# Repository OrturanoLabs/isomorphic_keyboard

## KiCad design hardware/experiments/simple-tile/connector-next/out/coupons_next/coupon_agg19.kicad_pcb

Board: 2 copper layers, 46 parts (0 on the bottom side), 19 nets.

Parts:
PB_W: PB_W
PB_clk: PB_clk
PB_data: PB_data
PB_first: PB_first
PB_latch: PB_latch
PGND: PGND
PGND_DET_B: PGND_DET_B
PGND_DET_R: PGND_DET_R
PGND_DET_T: PGND_DET_T
PL_clk: PL_clk
PL_data: PL_data
PL_endrow: PL_endrow
PL_latch: PL_latch
PR_latch: PR_latch
PT_W: PT_W
PT_clk: PT_clk
PT_data: PT_data
PT_endcol: PT_endcol
PVCC: PVCC
SW00, SW10, SW11, SW20, SW21, SW30, SW31: SW_Hotswap_Kailh_MX_1.00u
SW01: SW_Hotswap_Kailh_MX_1.00u_EdgeTrim
TPB_W: TPB_W
TPB_clk: TPB_clk
TPB_data: TPB_data
TPB_first: TPB_first
TPB_latch: TPB_latch
TPGND: TPGND
TPGND_DET_B: TPGND_DET_B
TPGND_DET_R: TPGND_DET_R
TPGND_DET_T: TPGND_DET_T
TPL_clk: TPL_clk
TPL_data: TPL_data
TPL_endrow: TPL_endrow
TPL_latch: TPL_latch
TPR_latch: TPR_latch
TPT_W: TPT_W
TPT_clk: TPT_clk
TPT_data: TPT_data
TPT_endcol: TPT_endcol
TPVCC: TPVCC

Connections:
B_W: PB_W.1, TPB_W.1
B_clk: PB_clk.1, TPB_clk.1
B_data: PB_data.1, TPB_data.1
B_first: PB_first.1, TPB_first.1
B_latch: PB_latch.1, TPB_latch.1
GND: PGND.1, TPGND.1
GND_DET_B: PGND_DET_B.1, TPGND_DET_B.1
GND_DET_R: PGND_DET_R.1, TPGND_DET_R.1
GND_DET_T: PGND_DET_T.1, TPGND_DET_T.1
L_clk: PL_clk.1, TPL_clk.1
L_data: PL_data.1, TPL_data.1
L_endrow: PL_endrow.1, TPL_endrow.1
L_latch: PL_latch.1, TPL_latch.1
R_latch: PR_latch.1, TPR_latch.1
T_W: PT_W.1, TPT_W.1
T_clk: PT_clk.1, TPT_clk.1
T_data: PT_data.1, TPT_data.1
T_endcol: PT_endcol.1, TPT_endcol.1
VCC: PVCC.1, TPVCC.1

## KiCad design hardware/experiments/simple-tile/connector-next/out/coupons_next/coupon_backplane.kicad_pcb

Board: 2 copper layers, 111 parts (0 on the bottom side), 54 nets.

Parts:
PA0: PA0
PA1: PA1
PA2: PA2
PA3: PA3
PA4: PA4
PA5: PA5
PA6: PA6
PA7: PA7
PA8: PA8
PA9: PA9
PA10: PA10
PA11: PA11
PA12: PA12
PA13: PA13
PA14: PA14
PA15: PA15
PA16: PA16
PA17: PA17
PA18: PA18
PR0: PR0
PR1: PR1
PR2: PR2
PR3: PR3
PR4: PR4
PR5: PR5
PR6: PR6
PR7: PR7
PR8: PR8
PR9: PR9
PR10: PR10
PR11: PR11
PR12: PR12
PR13: PR13
PR14: PR14
PR15: PR15
PR16: PR16
PR17: PR17
PR18: PR18
PS0: PS0
PS1: PS1
PS2: PS2
PS3: PS3
PS4: PS4
PS5: PS5
PS6: PS6
PS7: PS7
PS8: PS8
PS9: PS9
PS10: PS10
PS11: PS11
PS12: PS12
PS13: PS13
PS14: PS14
PS15: PS15
PS16: PS16
PS17: PS17
PS18: PS18
TPAB_W: TPAB_W
TPAB_clk: TPAB_clk
TPAB_data: TPAB_data
TPAB_latch: TPAB_latch
TPAGND: TPAGND
TPAGND_DET_R: TPAGND_DET_R
TPAGND_DET_T: TPAGND_DET_T
TPAL_clk: TPAL_clk
TPAL_data: TPAL_data
TPAL_endrow: TPAL_endrow
TPAL_latch: TPAL_latch
TPAR_latch: TPAR_latch
TPAT_W: TPAT_W
TPAT_clk: TPAT_clk
TPAT_data: TPAT_data
TPAT_endcol: TPAT_endcol
TPAVCC: TPAVCC
TPDA.GND_DET_B: TPDA.GND_DET_B
TPDS.GND_DET_R: TPDS.GND_DET_R
TPDS.GND_DET_T: TPDS.GND_DET_T
TPRB_W: TPRB_W
TPRB_clk: TPRB_clk
TPRB_data: TPRB_data
TPRB_first: TPRB_first
TPRB_latch: TPRB_latch
TPRGND: TPRGND
TPRGND_DET_B: TPRGND_DET_B
TPRGND_DET_R: TPRGND_DET_R
TPRGND_DET_T: TPRGND_DET_T
TPRL_clk: TPRL_clk
TPRL_data: TPRL_data
TPRL_latch: TPRL_latch
TPRR_latch: TPRR_latch
TPRT_W: TPRT_W
TPRT_clk: TPRT_clk
TPRT_data: TPRT_data
TPRT_endcol: TPRT_endcol
TPRVCC: TPRVCC
TPSB_W: TPSB_W
TPSB_clk: TPSB_clk
TPSB_data: TPSB_data
TPSB_first: TPSB_first
TPSB_latch: TPSB_latch
TPSGND: TPSGND
TPSGND_DET_B: TPSGND_DET_B
TPSL_clk: TPSL_clk
TPSL_data: TPSL_data
TPSL_endrow: TPSL_endrow
TPSL_latch: TPSL_latch
TPSR_latch: TPSR_latch
TPST_W: TPST_W
TPST_clk: TPST_clk
TPST_data: TPST_data
TPSVCC: TPSVCC

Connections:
SA.B_W: PA13.1, TPAB_W.1
SA.B_clk: PA9.1, TPAB_clk.1
SA.B_data: PA10.1, TPAB_data.1
SA.B_latch: PA12.1, TPAB_latch.1
SA.GND: PA0.1, TPAGND.1
SA.GND_DET_R: PA3.1, TPAGND_DET_R.1
SA.GND_DET_T: PA1.1, TPAGND_DET_T.1
SA.L_clk: PA14.1, TPAL_clk.1
SA.L_data: PA15.1, TPAL_data.1
SA.L_endrow: PA16.1, TPAL_endrow.1
SA.L_latch: PA17.1, TPAL_latch.1
SA.R_latch: PA18.1, TPAR_latch.1
SA.T_W: PA8.1, TPAT_W.1
SA.T_clk: PA5.1, TPAT_clk.1
SA.T_data: PA6.1, TPAT_data.1
SA.T_endcol: PA7.1, TPAT_endcol.1
SA.VCC: PA4.1, TPAVCC.1
SR.B_W: PR13.1, TPRB_W.1
SR.B_clk: PR9.1, TPRB_clk.1
SR.B_data: PR10.1, TPRB_data.1
SR.B_first: PR11.1, TPRB_first.1
SR.B_latch: PR12.1, TPRB_latch.1
SR.GND: PR0.1, TPRGND.1
SR.GND_DET_B: PR2.1, TPRGND_DET_B.1
SR.GND_DET_R: PR3.1, TPRGND_DET_R.1
SR.GND_DET_T: PR1.1, TPRGND_DET_T.1
SR.L_clk: PR14.1, TPRL_clk.1
SR.L_data: PR15.1, TPRL_data.1
SR.L_latch: PR17.1, TPRL_latch.1
SR.R_latch: PR18.1, TPRR_latch.1
SR.T_W: PR8.1, TPRT_W.1
SR.T_clk: PR5.1, TPRT_clk.1
SR.T_data: PR6.1, TPRT_data.1
SR.T_endcol: PR7.1, TPRT_endcol.1
SR.VCC: PR4.1, TPRVCC.1
SS.B_W: PS13.1, TPSB_W.1
SS.B_clk: PS9.1, TPSB_clk.1
SS.B_data: PS10.1, TPSB_data.1
SS.B_first: PS11.1, TPSB_first.1
SS.B_latch: PS12.1, TPSB_latch.1
SS.GND: PS0.1, TPSGND.1
SS.GND_DET_B: PS2.1, TPSGND_DET_B.1
SS.L_clk: PS14.1, TPSL_clk.1
SS.L_data: PS15.1, TPSL_data.1
SS.L_endrow: PS16.1, TPSL_endrow.1
SS.L_latch: PS17.1, TPSL_latch.1
SS.R_latch: PS18.1, TPSR_latch.1
SS.T_W: PS8.1, TPST_W.1
SS.T_clk: PS5.1, TPST_clk.1
SS.T_data: PS6.1, TPST_data.1
SS.VCC: PS4.1, TPSVCC.1
STUBDET.A.GND_DET_B>S.T_endcol: PA2.1, PS7.1, TPDA.GND_DET_B.1
STUBDET.S.GND_DET_R>R.L_endrow: PR16.1, PS3.1, TPDS.GND_DET_R.1
STUBDET.S.GND_DET_T>A.B_first: PA11.1, PS1.1, TPDS.GND_DET_T.1

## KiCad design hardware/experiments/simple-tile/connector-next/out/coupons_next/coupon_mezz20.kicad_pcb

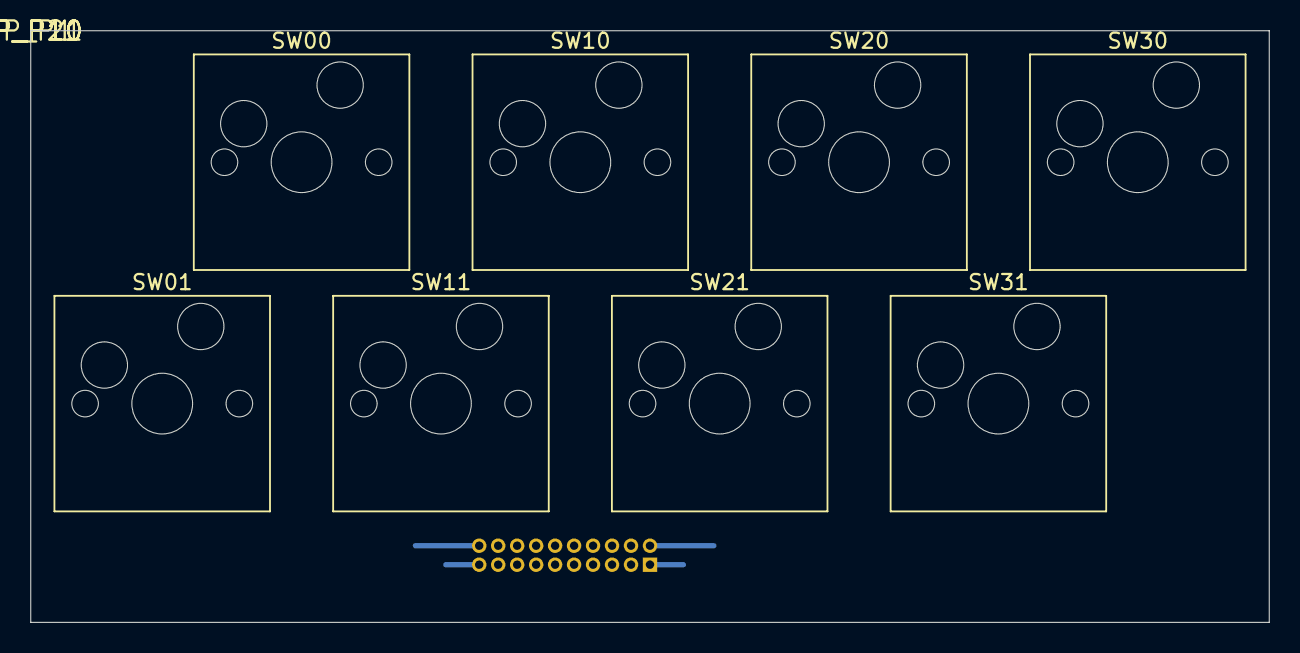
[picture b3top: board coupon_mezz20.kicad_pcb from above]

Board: 2 copper layers, 81.6 x 39.0 mm, 13 parts (1 on the bottom side), 4 nets.

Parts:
J1: G125-MVX2005L0X (tile plug, THT tails); Harwin_Gecko-G125-MVX2005L0X_2x10_P1.25mm_Vertical
SW00, SW10, SW11, SW20, SW21, SW30, SW31: SW_Hotswap_Kailh_MX_1.00u
SW01: SW_Hotswap_Kailh_MX_1.00u_EdgeTrim
TP_P1: TP_P1
TP_P10: TP_P10
TP_P11: TP_P11
TP_P20: TP_P20

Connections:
J1.B_W:10: J1.10, TP_P10.1
J1.GND:20: J1.20, TP_P20.1
J1.L_clk:11: J1.11, TP_P11.1
J1.VCC:1: J1.1, TP_P1.1

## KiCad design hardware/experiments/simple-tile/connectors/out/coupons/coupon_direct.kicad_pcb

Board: 2 copper layers, 14 parts (0 on the bottom side), 8 nets.

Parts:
MH: (no value)
MH#2: (no value)
SW00, SW10, SW11: Kailh hotswap; SW_Hotswap_Kailh_MX_1.00u
SW01: Kailh hotswap; SW_Hotswap_Kailh_MX_1.00u_EdgeTrim
TPK00_C: TPK00_C
TPK00_R: TPK00_R
TPK01_C: TPK01_C
TPK01_R: TPK01_R
TPK10_C: TPK10_C
TPK10_R: TPK10_R
TPK11_C: TPK11_C
TPK11_R: TPK11_R

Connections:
K00_C: SW00.2, TPK00_C.1
K00_R: SW00.1, TPK00_R.1
K01_C: SW01.2, TPK01_C.1
K01_R: SW01.1, TPK01_R.1
K10_C: SW10.2, TPK10_C.1
K10_R: SW10.1, TPK10_R.1
K11_C: SW11.2, TPK11_C.1
K11_R: SW11.1, TPK11_R.1

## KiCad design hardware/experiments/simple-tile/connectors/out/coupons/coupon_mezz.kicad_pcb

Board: 2 copper layers, 11 parts (1 on the bottom side), 4 nets.

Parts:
J1: DF12E3.0-30DP (tile plug); Hirose_DF12_DF12E3.0-30DP-0.5V_2x15_P0.50mm_Vertical
MH: (no value)
MH#2: (no value)
SW00, SW10, SW11: Kailh hotswap; SW_Hotswap_Kailh_MX_1.00u
SW01: Kailh hotswap; SW_Hotswap_Kailh_MX_1.00u_EdgeTrim
TP_P1: TP_P1
TP_P15: TP_P15
TP_P16: TP_P16
TP_P30: TP_P30

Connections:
J1.1: J1.1, TP_P1.1
J1.15: J1.15, TP_P15.1
J1.16: J1.16, TP_P16.1
J1.30: J1.30, TP_P30.1

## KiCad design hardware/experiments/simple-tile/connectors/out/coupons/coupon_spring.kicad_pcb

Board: 2 copper layers, 28 parts (0 on the bottom side), 11 nets.

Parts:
MH: (no value)
MH#2: (no value)
PJ103_1: PJ103_1
PJ103_2: PJ103_2
PJ103_3: PJ103_3
PJ103_4: PJ103_4
PJ103_5: PJ103_5
PJ103_6: PJ103_6
PJ103_7: PJ103_7
PJ103_8: PJ103_8
ST0a: ST0a
ST0b: ST0b
ST1a: ST1a
ST1b: ST1b
ST2a: ST2a
ST2b: ST2b
SW00, SW10, SW11: Kailh hotswap; SW_Hotswap_Kailh_MX_1.00u
SW01: Kailh hotswap; SW_Hotswap_Kailh_MX_1.00u_EdgeTrim
TPJ103_1: TPJ103_1
TPJ103_2: TPJ103_2
TPJ103_3: TPJ103_3
TPJ103_4: TPJ103_4
TPJ103_5: TPJ103_5
TPJ103_6: TPJ103_6
TPJ103_7: TPJ103_7
TPJ103_8: TPJ103_8

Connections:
J103.1: PJ103_1.1, TPJ103_1.1
J103.2: PJ103_2.1, TPJ103_2.1
J103.3: PJ103_3.1, TPJ103_3.1
J103.4: PJ103_4.1, TPJ103_4.1
J103.5: PJ103_5.1, TPJ103_5.1
J103.6: PJ103_6.1, TPJ103_6.1
J103.7: PJ103_7.1, TPJ103_7.1
J103.8: PJ103_8.1, TPJ103_8.1
STRAP0: ST0a.1, ST0b.1
STRAP1: ST1a.1, ST1b.1
STRAP2: ST2a.1, ST2b.1

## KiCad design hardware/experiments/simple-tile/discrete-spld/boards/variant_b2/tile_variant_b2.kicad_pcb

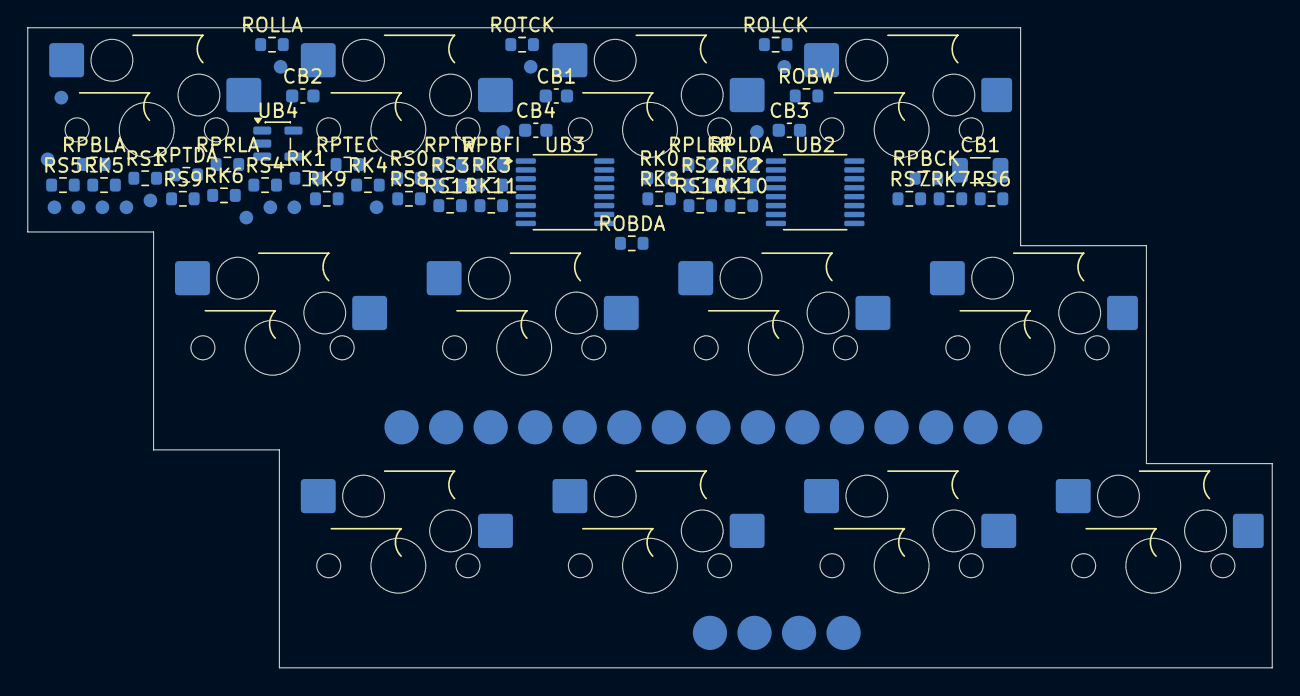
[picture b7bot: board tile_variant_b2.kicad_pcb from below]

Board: 2 copper layers, 90.8 x 46.7 mm, 93 parts (81 on the bottom side), 44 nets, no tracks yet.

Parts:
CB1, CB1#2: 100n; CB1
CB2: 100n; CB2
CB3: 100n; CB3
CB4: 100n; CB4
JP_B_W: PAD2.5; JP_B_W
JP_B_clk: PAD2.5; JP_B_clk
JP_B_data: PAD2.5; JP_B_data
JP_B_first: PAD2.5; JP_B_first
JP_B_latch: PAD2.5; JP_B_latch
JP_GND: PAD2.5; JP_GND
JP_GND_DET_B: PAD2.5; JP_GND_DET_B
JP_GND_DET_R: PAD2.5; JP_GND_DET_R
JP_GND_DET_T: PAD2.5; JP_GND_DET_T
JP_L_clk: PAD2.5; JP_L_clk
JP_L_data: PAD2.5; JP_L_data
JP_L_endrow: PAD2.5; JP_L_endrow
JP_L_latch: PAD2.5; JP_L_latch
JP_R_latch: PAD2.5; JP_R_latch
JP_T_W: PAD2.5; JP_T_W
JP_T_clk: PAD2.5; JP_T_clk
JP_T_data: PAD2.5; JP_T_data
JP_T_endcol: PAD2.5; JP_T_endcol
JP_VCC: PAD2.5; JP_VCC
RK0: 10k; RK0
RK1: 10k; RK1
RK2: 10k; RK2
RK3: 10k; RK3
RK4: 10k; RK4
RK5: 10k; RK5
RK6: 10k; RK6
RK7: 10k; RK7
RK8: 10k; RK8
RK9: 10k; RK9
RK10: 10k; RK10
RK11: 10k; RK11
ROBDA: 33; ROBDA
ROBW: 33; ROBW
ROLCK: 33; ROLCK
ROLLA: 33; ROLLA
ROTCK: 33; ROTCK
RPBCK: 10k; RPBCK
RPBFI: 10k; RPBFI
RPBLA: 10k; RPBLA
RPLDA: 10k; RPLDA
RPLER: 10k; RPLER
RPRLA: 10k; RPRLA
RPTDA: 10k; RPTDA
RPTEC: 10k; RPTEC
RPTW: 10k; RPTW
RS0: 100; RS0
RS1: 100; RS1
RS2: 100; RS2
RS3: 100; RS3
RS4: 100; RS4
RS5: 100; RS5
RS6: 100; RS6
RS7: 100; RS7
RS8: 100; RS8
RS9: 100; RS9
RS10: 100; RS10
RS11: 100; RS11
SW1: SW; SW1
SW2: SW; SW2
SW3: SW; SW3
SW4: SW; SW4
SW5: SW; SW5
SW6: SW; SW6
SW7: SW; SW7
SW8: SW; SW8
SW9: SW; SW9
SW10: SW; SW10
SW11: SW; SW11
SW12: SW; SW12
TP_B_W: B_W; TP_B_W
TP_B_clk: B_clk; TP_B_clk
TP_B_data: B_data; TP_B_data
TP_B_first: B_first; TP_B_first
TP_B_latch: B_latch; TP_B_latch
TP_GND: GND; TP_GND
TP_L_clk: L_clk; TP_L_clk
TP_L_data: L_data; TP_L_data
TP_L_latch: L_latch; TP_L_latch
TP_R_latch: R_latch; TP_R_latch
TP_T_clk: T_clk; TP_T_clk
TP_T_data: T_data; TP_T_data
TP_VCC: VCC; TP_VCC
TP_data_drv: data_drv; TP_data_drv
TP_latch_drv: latch_drv; TP_latch_drv
TP_nRST: nRST; TP_nRST
UB2: SN74LVC165A; UB2
UB3: SN74LVC165A; UB3
UB4: SN74LVC1G04; UB4

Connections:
B_W: JP_B_W.1, ROBW.2, TP_B_W.1
B_clk: JP_B_clk.1, RPBCK.1, TP_B_clk.1, UB2.2, UB3.2
B_data: JP_B_data.1, ROBDA.2, TP_B_data.1
B_first: JP_B_first.1, RPBFI.1, TP_B_first.1
B_latch: JP_B_latch.1, RPBLA.1, TP_B_latch.1
CHAIN: UB2.9, UB3.10
GND: CB1.2, CB1#2.2, CB2.2, CB3.2, CB4.2, JP_GND.1, JP_GND_DET_B.1, JP_GND_DET_R.1, JP_GND_DET_T.1, RK0.2, RK1.2, RK2.2, RK3.2, RK4.2, RK5.2, RK6.2, RK7.2, RK8.2, RK9.2, RK10.2, RK11.2, RPBLA.2, RPLDA.2, RPRLA.2, RPTDA.2, TP_GND.1, UB2.8, UB2.15, UB3.8, UB3.15
KEY0: RS0.2, UB3.6
KEY1: RS1.2, UB3.5
KEY2: RS2.2, UB3.4
KEY3: RS3.2, UB3.3
KEY4: RS4.2, UB3.14
KEY5: RS5.2, UB3.13
KEY6: RS6.2, UB3.12
KEY7: RS7.2, UB3.11
KEY8: RS8.2, UB2.6
KEY9: RS9.2, UB2.5
KEY10: RS10.2, UB2.4
KEY11: RS11.2, UB2.3
L_clk: JP_L_clk.1, ROLCK.2, TP_L_clk.1
L_data: JP_L_data.1, RPLDA.1, TP_L_data.1
L_endrow: JP_L_endrow.1, RPLER.1, UB2.12
L_latch: JP_L_latch.1, ROLLA.2, TP_L_latch.1
R_latch: JP_R_latch.1, RPRLA.1, TP_R_latch.1
SWN0: RK0.1, RS0.1, SW1.2
SWN1: RK1.1, RS1.1, SW2.2
SWN2: RK2.1, RS2.1, SW3.2
SWN3: RK3.1, RS3.1, SW4.2
SWN4: RK4.1, RS4.1, SW5.2
SWN5: RK5.1, RS5.1, SW6.2
SWN6: RK6.1, RS6.1, SW7.2
SWN7: RK7.1, RS7.1, SW8.2
SWN8: RK8.1, RS8.1, SW9.2
SWN9: RK9.1, RS9.1, SW10.2
SWN10: RK10.1, RS10.1, SW11.2
SWN11: RK11.1, RS11.1, SW12.2
T_W: JP_T_W.1, RPTW.1
T_clk: JP_T_clk.1, ROTCK.2, TP_T_clk.1
T_data: JP_T_data.1, RPTDA.1, TP_T_data.1
T_endcol: JP_T_endcol.1, RPTEC.1, UB2.11
VCC: CB1.1, CB1#2.1, CB2.1, CB3.1, CB4.1, JP_VCC.1, RPBCK.2, RPBFI.2, RPLER.2, RPTEC.2, RPTW.2, SW1.1, SW2.1, SW3.1, SW4.1, SW5.1, SW6.1, SW7.1, SW8.1, SW9.1, SW10.1, SW11.1, SW12.1, TP_VCC.1, UB2.13, UB2.14, UB2.16, UB3.16
data_drv: ROBDA.1, TP_data_drv.1, UB3.9
latch_drv: ROLLA.1, TP_latch_drv.1, UB4.2
nRST: TP_nRST.1, UB2.1, UB3.1, UB4.4

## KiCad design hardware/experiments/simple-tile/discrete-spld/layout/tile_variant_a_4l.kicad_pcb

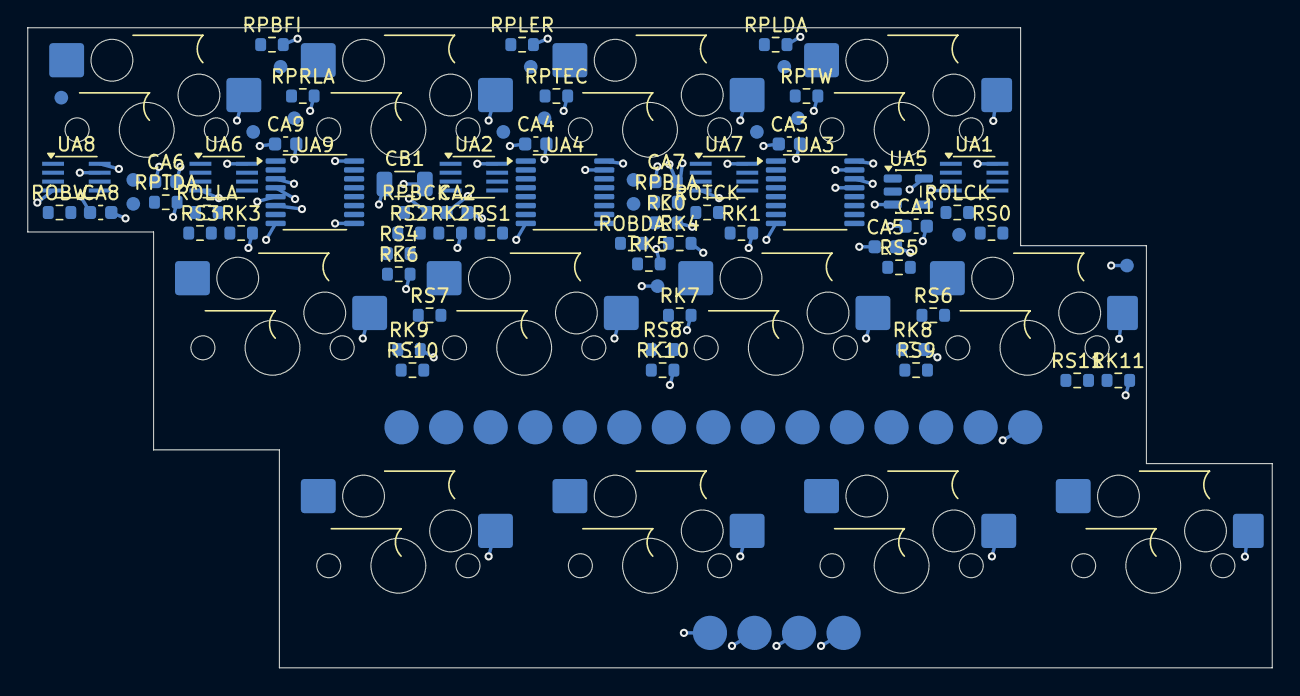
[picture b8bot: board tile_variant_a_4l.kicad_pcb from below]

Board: 4 copper layers, 90.8 x 46.7 mm, 105 parts (93 on the bottom side), 52 nets.

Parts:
CA1: 100n; CA1
CA2: 100n; CA2
CA3: 100n; CA3
CA4: 100n; CA4
CA5: 100n; CA5
CA6: 100n; CA6
CA7: 100n; CA7
CA8: 100n; CA8
CA9: 100n; CA9
CB1: 4u7; CB1
JP_B_W: PAD2.5; JP_B_W
JP_B_clk: PAD2.5; JP_B_clk
JP_B_data: PAD2.5; JP_B_data
JP_B_first: PAD2.5; JP_B_first
JP_B_latch: PAD2.5; JP_B_latch
JP_GND: PAD2.5; JP_GND
JP_GND_DET_B: PAD2.5; JP_GND_DET_B
JP_GND_DET_R: PAD2.5; JP_GND_DET_R
JP_GND_DET_T: PAD2.5; JP_GND_DET_T
JP_L_clk: PAD2.5; JP_L_clk
JP_L_data: PAD2.5; JP_L_data
JP_L_endrow: PAD2.5; JP_L_endrow
JP_L_latch: PAD2.5; JP_L_latch
JP_R_latch: PAD2.5; JP_R_latch
JP_T_W: PAD2.5; JP_T_W
JP_T_clk: PAD2.5; JP_T_clk
JP_T_data: PAD2.5; JP_T_data
JP_T_endcol: PAD2.5; JP_T_endcol
JP_VCC: PAD2.5; JP_VCC
RK0: 10k; RK0
RK1: 10k; RK1
RK2: 10k; RK2
RK3: 10k; RK3
RK4: 10k; RK4
RK5: 10k; RK5
RK6: 10k; RK6
RK7: 10k; RK7
RK8: 10k; RK8
RK9: 10k; RK9
RK10: 10k; RK10
RK11: 10k; RK11
ROBDA: 33; ROBDA
ROBW: 33; ROBW
ROLCK: 33; ROLCK
ROLLA: 33; ROLLA
ROTCK: 33; ROTCK
RPBCK: 10k; RPBCK
RPBFI: 10k; RPBFI
RPBLA: 10k; RPBLA
RPLDA: 10k; RPLDA
RPLER: 10k; RPLER
RPRLA: 10k; RPRLA
RPTDA: 10k; RPTDA
RPTEC: 10k; RPTEC
RPTW: 10k; RPTW
RS0: 100; RS0
RS1: 100; RS1
RS2: 100; RS2
RS3: 100; RS3
RS4: 100; RS4
RS5: 100; RS5
RS6: 100; RS6
RS7: 100; RS7
RS8: 100; RS8
RS9: 100; RS9
RS10: 100; RS10
RS11: 100; RS11
SW1: SW; SW1
SW2: SW; SW2
SW3: SW; SW3
SW4: SW; SW4
SW5: SW; SW5
SW6: SW; SW6
SW7: SW; SW7
SW8: SW; SW8
SW9: SW; SW9
SW10: SW; SW10
SW11: SW; SW11
SW12: SW; SW12
TP_B_W: B_W; TP_B_W
TP_B_clk: B_clk; TP_B_clk
TP_B_data: B_data; TP_B_data
TP_B_first: B_first; TP_B_first
TP_B_latch: B_latch; TP_B_latch
TP_GND: GND; TP_GND
TP_L_clk: L_clk; TP_L_clk
TP_L_data: L_data; TP_L_data
TP_L_latch: L_latch; TP_L_latch
TP_R_latch: R_latch; TP_R_latch
TP_T_clk: T_clk; TP_T_clk
TP_T_data: T_data; TP_T_data
TP_VCC: VCC; TP_VCC
TP_W: W; TP_W
TP_data_drv: data_drv; TP_data_drv
TP_latch_drv: latch_drv; TP_latch_drv
TP_nRST: nRST; TP_nRST
UA1: SN74LVC2G126; UA1
UA2: SN74LVC2G08; UA2
UA3: SN74LVC165A; UA3
UA4: SN74LVC165A; UA4
UA5: SN74LVC1G04; UA5
UA6: SN74LVC2G32; UA6
UA7: SN74LVC2G125; UA7
UA8: SN74LVC2G74; UA8
UA9: SN74LV161A; UA9

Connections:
B_W: JP_B_W.1, ROBW.2, TP_B_W.1
B_W_drv: ROBW.1, UA6.5, UA8.5
B_clk: JP_B_clk.1, RPBCK.1, TP_B_clk.1, UA1.2, UA3.2, UA4.2, UA7.2, UA8.1, UA9.2
B_data: JP_B_data.1, ROBDA.2, TP_B_data.1
B_first: JP_B_first.1, RPBFI.1, TP_B_first.1, UA2.6
B_latch: JP_B_latch.1, RPBLA.1, TP_B_latch.1, UA6.1
CHAIN: UA3.9, UA4.10
DS_net: UA1.3, UA3.10, UA7.3
GND: CA1.2, CA2.2, CA3.2, CA4.2, CA5.2, CA6.2, CA7.2, CA8.2, CA9.2, CB1.2, JP_GND.1, JP_GND_DET_B.1, JP_GND_DET_R.1, JP_GND_DET_T.1, RK0.2, RK1.2, RK2.2, RK3.2, RK4.2, RK5.2, RK6.2, RK7.2, RK8.2, RK9.2, RK10.2, RK11.2, RPBLA.2, RPLDA.2, RPRLA.2, RPTDA.2, TP_GND.1, UA1.4, UA2.4, UA3.8, UA3.15, UA4.8, UA4.15, UA5.3, UA6.4, UA7.4, UA8.4, UA9.3, UA9.4, UA9.5, UA9.6, UA9.8
KEY0: RS0.2, UA4.6
KEY1: RS1.2, UA4.5
KEY2: RS2.2, UA4.4
KEY3: RS3.2, UA4.3
KEY4: RS4.2, UA4.14
KEY5: RS5.2, UA4.13
KEY6: RS6.2, UA4.12
KEY7: RS7.2, UA4.11
KEY8: RS8.2, UA3.6
KEY9: RS9.2, UA3.5
KEY10: RS10.2, UA3.4
KEY11: RS11.2, UA3.3
L_clk: JP_L_clk.1, ROLCK.2, TP_L_clk.1
L_clk_drv: ROLCK.1, UA1.6
L_data: JP_L_data.1, RPLDA.1, TP_L_data.1, UA1.5
L_endrow: JP_L_endrow.1, RPLER.1, UA3.12
L_latch: JP_L_latch.1, ROLLA.2, TP_L_latch.1
R_latch: JP_R_latch.1, RPRLA.1, TP_R_latch.1, UA6.2
SWN0: RK0.1, RS0.1, SW1.2
SWN1: RK1.1, RS1.1, SW2.2
SWN2: RK2.1, RS2.1, SW3.2
SWN3: RK3.1, RS3.1, SW4.2
SWN4: RK4.1, RS4.1, SW5.2
SWN5: RK5.1, RS5.1, SW6.2
SWN6: RK6.1, RS6.1, SW7.2
SWN7: RK7.1, RS7.1, SW8.2
SWN8: RK8.1, RS8.1, SW9.2
SWN9: RK9.1, RS9.1, SW10.2
SWN10: RK10.1, RS10.1, SW11.2
SWN11: RK11.1, RS11.1, SW12.2
T_W: JP_T_W.1, RPTW.1, UA2.5
T_clk: JP_T_clk.1, ROTCK.2, TP_T_clk.1
T_clk_drv: ROTCK.1, UA7.6
T_data: JP_T_data.1, RPTDA.1, TP_T_data.1, UA7.5
T_endcol: JP_T_endcol.1, RPTEC.1, UA3.11
Tc: UA2.2, UA9.15
VCC: CA1.1, CA2.1, CA3.1, CA4.1, CA5.1, CA6.1, CA7.1, CA8.1, CA9.1, CB1.1, JP_VCC.1, RPBCK.2, RPBFI.2, RPLER.2, RPTEC.2, RPTW.2, SW1.1, SW2.1, SW3.1, SW4.1, SW5.1, SW6.1, SW7.1, SW8.1, SW9.1, SW10.1, SW11.1, SW12.1, TP_VCC.1, UA1.8, UA2.8, UA3.13, UA3.14, UA3.16, UA4.16, UA5.5, UA6.8, UA7.8, UA8.7, UA8.8, UA9.9, UA9.16
W: TP_W.1, UA1.1, UA1.7, UA2.3, UA7.1, UA7.7
data_drv: ROBDA.1, TP_data_drv.1, UA2.1, UA4.9
flag_and: UA2.7, UA6.6
flag_d: UA6.3, UA8.2
latch_drv: ROLLA.1, TP_latch_drv.1, UA5.2, UA6.7
nRST: TP_nRST.1, UA3.1, UA4.1, UA5.4, UA8.6, UA9.1, UA9.7, UA9.10
